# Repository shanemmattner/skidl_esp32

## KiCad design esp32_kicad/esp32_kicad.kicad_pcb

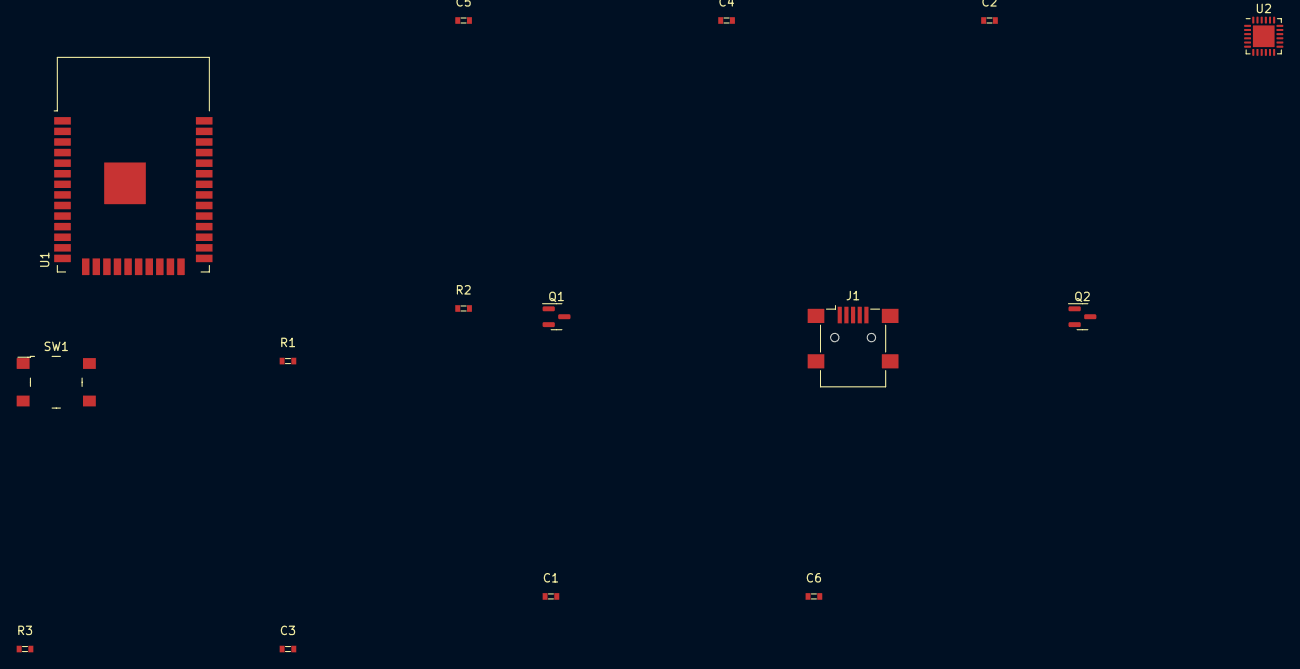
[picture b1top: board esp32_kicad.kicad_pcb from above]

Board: 2 copper layers, 15 parts (0 on the bottom side), 16 nets, no tracks yet.

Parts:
C1, C4: 100nF; 0603
C2, C3, C5: 10uF; 0603
C6: 4.7uF; 0603
J1: USB_B_Mini; USB_Mini-B_Lumberg_2486_01_Horizontal
Q1, Q2: DMN2041L; SOT-23
R1: 10k; 0603
R2, R3: 470R; 0603
SW1: SW_DPST; Switch_Tactile_SMD_6x6mm_PTS645
U1: ESP32-WROOM-32
U2: CP2104; QFN-24-1EP_4x4mm_P0.5mm_EP2.6x2.6mm

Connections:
DTR: Q1.3, Q2.1
GND: C4.2, C5.2, C6.2, J1.5, J1.6, U2.2, U2.25
GND_1: C1.2, C2.2, C3.2, SW1.3, SW1.4, U1.1
unnamed: C3.1, Q2.2, R1.2, SW1.1, SW1.2, U1.3
unnamed: J1.1, U2.8
unnamed: J1.2, U2.4
unnamed: J1.3, U2.3
unnamed: C6.1, U2.16
unnamed: Q1.2, U1.25
unnamed: R2.1, U1.35
unnamed: R2.2, U2.20
unnamed: R3.1, U1.34
unnamed: R3.2, U2.21
RTS: Q1.1, Q2.3
V3_3: C4.1, C5.1, U2.5, U2.6, U2.7
V3_3_1: C1.1, C2.1, R1.1, U1.2

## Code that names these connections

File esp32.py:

from skidl import *


# standard logic level FET
def npn_LL(gate, drain, source, sch_lib='Transistor_FET', sch_name='DMN2041L', footprint='Package_TO_SOT_SMD:SOT-23'):
    npn = Part(sch_lib, sch_name, footprint=footprint)
    npn[1] += gate
    npn[2] += source
    npn[3] += drain
    
def r(value, p1, p2, footprint='digikey-footprints:0603'):
    r = Part('Device', 'R', value=value, footprint=footprint)
    r[1] += p1
    r[2] += p2
    
def c(value, p1, p2, footprint='digikey-footprints:0603'):
    c = Part('Device', 'C', value=value, footprint=footprint)
    c[1] += p1
    c[2] += p2
    
def serial_to_usb(MCU_EN, GPIO0, MCU_TX, MCU_RX, V3_3=Net('V3_3'), GND=Net('GND')):

    # Make parts
    cp2104 = Part('Interface_USB','CP2104', footprint='Package_DFN_QFN:QFN-24-1EP_4x4mm_P0.5mm_EP2.6x2.6mm')
    # Connect power pins
    cp2104[5,6,7] += V3_3
    cp2104[2,25] += GND
    
    usb_conn = Part('Connector', 'USB_B_Mini', footprint='USB_Mini-B_Lumberg_2486_01_Horizontal')
    usb_conn['VBUS'] += cp2104[8]
    usb_conn['D-'] += cp2104[4]
    usb_conn['D+'] += cp2104[3]
    # usb_conn['ID'] # not connected
    usb_conn['GND','Shield'] += GND
    
    
    # Decoupling/bulking capacitors
    c('100nF', V3_3, GND)
    c('10uF', V3_3, GND)
    
    # ROM programming cap
    c('4.7uF', cp2104['VPP'], GND)
    
    # Nets for programming 
    RTS = Net('RTS')
    DTR = Net('DTR')
    #programming transistors
    npn_LL(RTS, DTR, GPIO0)
    npn_LL(DTR, RTS, MCU_EN)
    
    # uart resistors
    r('470R', MCU_TX, cp2104[20])
    r('470R', MCU_RX, cp2104[21])

def esp32_circuit(V3_3=Net('V3_3'), GND=Net('GND')):
    # MCU
    esp32 = Part('RF_Module','ESP32-WROOM-32', footprint='RF_Module:ESP32-WROOM-32')

    esp32[1] += GND
    esp32[2] += V3_3
    
    # Decoupling/bulking capacitors
    c('100nF', V3_3, GND)
    c('10uF', V3_3, GND)
    
    # Enable Circuit
    r('10k', V3_3, esp32[3])
    c('10uF', esp32[3], GND)
    switch = Part('Switch','SW_DPST', footprint='digikey-footprints:Switch_Tactile_SMD_6x6mm_PTS645')
    switch[1,2] += esp32['EN']
    switch[3,4] += GND

    # serial/programming
    serial_to_usb(esp32['EN'], esp32['IO0'], esp32['TXD0/IO1'], esp32['RXD0/IO3'])


esp32_circuit()



generate_netlist(file_="/home/shanemattner/Desktop/esp32/skidl_esp32/esp32_kicad/esp32.net")

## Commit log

2022-07-06 Starting project
2022-07-10 working example
2022-07-10 building esp32 circuit
